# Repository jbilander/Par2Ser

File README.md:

# Amiga Par2Ser device

> 🚧 **Status: Proof of concept — working, not yet fast.** The link is
> verified end-to-end on real Rev 2A hardware in both directions: interactive
> terminal traffic and **kermit file transfers** both work (a 512 KB ROM image
> and a 906 KB binary have been transferred with essentially zero packet
> errors). Current throughput is roughly **3400 CPS transmit / 1400 CPS
> receive** (release build). That is not yet a win over the built-in serial
> port — a stock A500 runs kermit at 38400 baud (~3800 CPS) via `8n1.device` —
> so **throughput optimization is the active work**; the whole point of going
> through the parallel port is to beat that comfortably. There are no tagged
> releases until it does, so **build at your own risk** and expect the design
> to still change. PRs and issues welcome.

***
Rev. 2A <br />

***

A `serial.device`-compatible Amiga driver that bridges the parallel port to a
USB FIFO (FT240X) via Niklas Ekström's 2E parallel-adapter protocol, so unmodified
comms programs (c-kermit, NComm, …) can `set line par2ser.device`.

The hardware side is a small board built around a Lattice **LC4064V-75TN48C**
CPLD that speaks the 2E protocol to the Amiga and presents the bytes to an
**FT240X** USB FIFO. The PC sees a standard USB serial port (VCP).

## Repository layout

- **`amiga/`** — `par2ser.device` driver source (m68k, Bartman gcc).
- **`cpld/`** — Verilog firmware for the Lattice LC4064V CPLD.
  - `rtl/` — design sources (`par2ser_top.v`, `par2ser_fsm.v`).
  - `sim/` — Icarus Verilog smoke testbench.
  - `isplever/` — Lattice ispLEVER Classic 2.1 project files and pin
    constraints (`Par2Ser.lci`).
- **`KiCad/`** — KiCad 5.1 schematic and PCB sources (Rev 2A).
- **`FT_PROG/`** — FT_PROG template (`Par2Ser.xml`) capturing the
  FT240X MTP settings the bridge needs (VCP enabled, CBUS5 → CLK12MHz,
  product description). Open it in FT_PROG and apply to a fresh
  board to skip the manual click-through.
- **`images/`** — board photos and screenshots used in this README.
- **`Par2Ser_rev2a_schematic.pdf`** — exported schematic for quick
  reference without opening KiCad.

## Hardware overview (Rev 2A)

- **Lattice LC4064V-75TN48C** CPLD (48-pin TQFP, 64 macrocells, -75 speed)
- **FTDI FT240X** USB-to-parallel-FIFO (SSOP-24), USB-C connector
- **8-bit bidirectional buffer** between the Amiga DB-25 and the CPLD
- **JTAG header** for programming the CPLD via ispVM System with a
  cheap FT4232H-mini-module-based cable

The driver is built in the style of [SimpleDevice](https://github.com/jbilander/SimpleDevice)
for the Bartman `m68k-amiga-elf` (gcc 15.1) toolchain. The serial machinery
(receive ring buffer, `CMD_READ` satisfied from buffer, `SDCMD_QUERY` count
from a software counter) is ported from Iain Barclay's `8n1.device` 43.5.

It targets **Kickstart 1.3** (and up): the sources include `<ks13_compat.h>`,
which uses `#pragma GCC poison` to turn any accidental call to a KS 2.0+
library function into a compile error, so the driver stays loadable on an
unexpanded A500/A2000.

## Bill of Materials (Rev 2A)

Sourcing notes: most actives and precision passives are from
[Mouser](https://www.mouser.com/), the connectors and decorative
LEDs are inexpensive enough to come from AliExpress sellers (linked
examples below — any equivalent footprint works). Generic 0805/0603
passives can be substituted with any reputable manufacturer's part
matching the value, package, and dielectric/tolerance noted.

| Ref               | Qty | Value / Part         | Description                                    | Package        | Source                                                                                          | Notes                                                       |
|-------------------|-----|----------------------|------------------------------------------------|----------------|-------------------------------------------------------------------------------------------------|-------------------------------------------------------------|
| **U1**            | 1   | LC4064V-75TN48C      | Lattice ispMACH 4000V CPLD                     | 48-TQFP        | [Mouser 842-LC4064V75TN48C](https://www.mouser.com/ProductDetail/842-LC4064V75TN48C)             | 64 macrocells, -75 speed grade                              |
| **U2**            | 1   | FT240XS-R            | FTDI USB-to-parallel FIFO                      | SSOP-24        | [Mouser 895-FT240XS-R](https://www.mouser.com/ProductDetail/895-FT240XS-R)                       | USB 2.0 Full Speed; VCP driver                              |
| **U3**            | 1   | TLV75533PDBVR        | TI 3.3 V LDO regulator, 500 mA                 | SOT-23-5       | [Mouser 595-TLV75533PDBVR](https://www.mouser.com/ProductDetail/595-TLV75533PDBVR)               | Fixed 3.3 V output                                          |
| **J1**            | 1   | DB25 Male            | Right-angle PCB DB-25 (M)                      | Solder cups   | [AliExpress example](https://www.aliexpress.com/item/1005006354086316.html)                      | Amiga parallel port                                         |
| **J2**            | 1   | USB-C 2.0 (TYPE-C-02) | 16-pin USB-C, USB 2.0 only (no SuperSpeed)    | SMD + THM tabs | [AliExpress example](https://www.aliexpress.com/item/1005005371954812.html)                      | Common "TYPE-C-02" footprint                                |
| **J3**            | 1   | 2×5 pin header       | 2.54 mm pitch, 10-pin (2×5)                    | Through-hole   | [AliExpress example](https://www.aliexpress.com/item/1005001493183557.html)                      | Optional — can press-fit ribbon during programming          |
| **FB1**           | 1   | 600 Ω @ 100 MHz       | Ferrite bead                                   | 0805           | [Mouser 875-HZ0805E601R-10](https://www.mouser.com/ProductDetail/875-HZ0805E601R-10)              | USB VBUS filter                                             |
| **D1**            | 1   | Yellow LED           | Activity LED (optional)                        | 2×5×7 mm TH    | [AliExpress example](https://www.aliexpress.com/item/1005006220921860.html)                      | Lit when transaction in progress                            |
| **D2**            | 1   | Green LED            | Power LED (optional)                           | 2×5×7 mm TH    | [AliExpress example](https://www.aliexpress.com/item/1005006220921860.html)                      | 3.3 V rail indicator                                        |
| **D3**            | 1   | Red LED              | TX LED                                         | 0603 SMD       | [AliExpress example](https://www.aliexpress.com/item/1005005975741298.html)                      | Amiga → PC byte flow                                        |
| **D4**            | 1   | Red LED              | RX LED                                         | 0603 SMD       | [AliExpress example](https://www.aliexpress.com/item/1005005975741298.html)                      | PC → Amiga byte flow                                        |
| **RN1**           | 1   | 8×10 kΩ bussed (A09-103JP) | 9-pin SIP resistor network               | SIP-9          | [AliExpress example](https://www.aliexpress.com/item/1005006954621214.html)                      | Amiga D0..D7 pull-ups, one common                           |
| **RN2**           | 1   | 4×10 kΩ bussed (A05-103JP) | 5-pin SIP resistor network               | SIP-5          | [AliExpress example](https://www.aliexpress.com/item/1005006954621214.html)                      | Additional Amiga-side pull-ups                              |
| **RN3, RN4, RN5** | 3   | 4×330 Ω isolated     | 8-pin SMD isolated resistor array              | 1206-8         | [Mouser 652-CAY16-3300F4LF](https://www.mouser.com/ProductDetail/652-CAY16-3300F4LF)              | Series limiters on signal lines                             |
| **R1, R3, R4**    | 3   | 1 kΩ                 | LED current limiter / signal                   | 0805           | [Mouser 652-CR0805FX-1001ELF](https://www.mouser.com/ProductDetail/652-CR0805FX-1001ELF)          |                                                             |
| **R2**            | 1   | 10 kΩ                | Series for D2 power LED (high R = low brightness) | 0805        | [Mouser 652-CR0805FX-1002ELF](https://www.mouser.com/ProductDetail/652-CR0805FX-1002ELF)          | Matches green power-LED forward voltage                     |
| **R5**            | 1   | 33 Ω                 | CLKOUT line damping resistor                   | 0603           | [Mouser 652-CR0603FX-33R0ELF](https://www.mouser.com/ProductDetail/652-CR0603FX-33R0ELF)          | Common practice for clock lines, not per FT240X datasheet  |
| **R6**            | 0   | 330 Ω (**DNP**)      | Series on /STROBE — not populated              | 0805           | [Mouser 652-CR0805FX-3300ELF](https://www.mouser.com/ProductDetail/652-CR0805FX-3300ELF)          | **Do Not Place** — populate only if /STROBE used in fw      |
| **R7, R8**        | 2   | 5.1 kΩ               | USB-C CC1/CC2 pull-downs                       | 0805           | [Mouser 652-CR0805FX-5101ELF](https://www.mouser.com/ProductDetail/652-CR0805FX-5101ELF)          | Identifies device as USB 2.0 (sink)                         |
| **R9, R10**       | 2   | 27 Ω                 | USB D+/D− series                               | 0805           | [Mouser 652-CR0805FX-27R0ELF](https://www.mouser.com/ProductDetail/652-CR0805FX-27R0ELF)          | Per USB 2.0 Full Speed spec                                 |
| **R11**           | 1   | 4.7 kΩ               | Pull-down for TCK (JTAG)                       | 0805           | [Mouser 652-CR0805FX-4701ELF](https://www.mouser.com/ProductDetail/652-CR0805FX-4701ELF)          | Standard JTAG practice                                      |
| **R12**           | 1   | 10 kΩ                | Pull-up for SIWU#                              | 0603           | [Mouser 652-CR0603-JW-103ELF](https://www.mouser.com/ProductDetail/652-CR0603-JW-103ELF)          | Keeps SIWU# deasserted when CPLD pin 44 is high-Z           |
| **C1, C2**        | 2   | 4.7 µF, 10 V, X7R    | VBUS bulk / LDO input                          | 0805           | [Mouser 81-GRM21BR71A475KE1K](https://www.mouser.com/ProductDetail/81-GRM21BR71A475KE1K)          | Murata GRM21 X7R, 10 V                                      |
| **C3**            | 1   | 1 µF, X7R            | LDO output filter                              | 0805           |                                                                                                 | Per TLV75533 datasheet                                      |
| **C4, C5**        | 2   | 47 pF, C0G/NP0       | USB D+/D− noise filter                         | 0603           | [Mouser 791-0603N470G160CT](https://www.mouser.com/ProductDetail/791-0603N470G160CT)              | Tight tolerance important                                   |
| **C6, C7, C8**    | 3   | 0.1 µF, X7R          | Decoupling (0805 spots)                        | 0805           |                                                                                                 |                                                             |
| **C9 – C13**      | 5   | 0.1 µF, X7R          | Decoupling (0603 spots)                        | 0603           |                                                                                                 | One per VCC pin                                             |

**Distinct line items: 27** &nbsp;·&nbsp; **Components to populate: 37** (38 if /STROBE is wired up in a future firmware — see R6)

### Mounting and additional hardware

- The **LC4064V** is JTAG-programmable in-circuit — no socket needed.
- The **JTAG header (J3)** uses the standard Lattice 2×5 pinout —
  check `cpld/README.md` for the exact pinout and the recommended
  FT4232H-Mini-Module-based cable. The header doesn't have to be
  soldered down; you can press-and-hold the 2×5 ribbon cable
  against the pads during programming.

### 3D-printable case

A 3D-printable two-part case is provided in the `3D/` folder. It is
adapted from the former **SDBox-v2** case, slimmed down and made more
proportional — the Rev 2A design no longer has to house a bulky
Arduino Nano v3, so the enclosure is significantly thinner. The DB-25
exits one end and the USB-C port the other, and the top lid has two
holes for the panel LEDs: one for the **Power LED (green)** and one for
the **Activity LED (yellow)**.

| File | Description |
|------|-------------|
| `3D/Par2Ser.scdoc` | SpaceClaim source file for the case |
| `3D/Par2Ser.stp` | STEP export (top + bottom) for use in other CAD tools |
| `3D/Par2Ser_top.stl` | Top lid, ready to slice and print |
| `3D/Par2Ser_bottom.stl` | Bottom shell, ready to slice and print |
| `3D/Par2Ser_text.skp` | SketchUp source for the embossed "Par2Ser" lid text |

<table>
  <tr>
    <td align="center">
      <br />
      <sub>USB-C end, with the two LED holes in the top lid</sub>
    </td>
    <td align="center">
      <br />
      <sub>DB-25 end</sub>
    </td>
  </tr>
  <tr>
    <td align="center">
      <br />
      <sub>Side profile showing the slimmer enclosure</sub>
    </td>
    <td align="center">
      <br />
      <sub>PCB fitted into the bottom shell</sub>
    </td>
  </tr>
</table>

The renders above are from the CAD program. The case was printed on a
Creality Ender-3 Pro in white PLA. The build photos below show the
assembly steps and the finished unit fitted to an Amiga 500.

#### Fitting the panel LEDs

The two indicator LEDs are soldered last. Fit the **PWR (green, Power)**
and **ACT (yellow, Activity)** LEDs into their positions, then check
from the top that each one protrudes ever so slightly through its hole
in the case lid. Once the height looks right, tack down a single leg,
snip the leads flush, and only then solder both joints properly. Doing
it in that order keeps the LEDs sitting at the correct height instead of
being pushed in or standing too proud.

<table>
  <tr>
    <td align="center">
      <br />
      <sub>Test-fitting the green PWR and yellow ACT LEDs before tacking them down</sub>
    </td>
    <td align="center">
      <br />
      <sub>Underside of the finished board seated in the bottom shell</sub>
    </td>
  </tr>
</table>

#### Finished unit

<table>
  <tr>
    <td align="center">
      <br />
      <sub>Assembled case closed up, with the PWR/ACT LEDs visible through the lid</sub>
    </td>
    <td align="center">
      <br />
      <sub>Plugged into the A500 parallel port and connected to a PC over USB-C</sub>
    </td>
  </tr>
</table>

In the powered-on photo the green **PWR** LED is lit, and the red glow
bleeding through the lid is the FT240XS **RX/TX** LEDs shining through
the white PLA — here the blink firmware has the **TX** LED on. This is
something of a happy accident: if you don't want the glow, print the
case in black or another dark material, or simply leave the RX/TX LEDs
unpopulated.

> **Note:** The USB-C cut-out in the current print is slightly too wide.
> It's a cosmetic issue only — the port works fine — and will be tidied
> up shortly so the opening sits more symmetrically around the connector.

## Files (amiga/)

- `par2ser.c` — device skeleton + serial command set + receive ring buffer
- `transport.h` / `transport.c` — byte-pipe to the adapter (**stubbed** for now)
- `debug.c` — `KPrintF` over `RawDoFmt`/`RawPutChar` (verbatim from SimpleDevice)
- `Makefile`

## Build (amiga/)

```sh
cd amiga
make debug      # build-debug/par2ser.device, with KPrintF tracing
make release    # build-release/par2ser.device, stripped
```

Adjust `INCDIRS` for your NDK path as in SimpleDevice.

## Programming the FT240X (one-time, before first use)

The CPLD needs a 12 MHz clock from the FT240X to operate. By default
the FT240X's CBUS5 pin is **not** configured as a clock output — you
have to set its function in the chip's internal MTP (one-time-programmable)
memory using FTDI's **FT_PROG** utility. While you're at it, you should
also tell the chip to advertise itself as a Virtual COM Port (VCP) so
that comms software on the host can open it as a regular serial port,
and you can optionally set a friendly USB product-description string.

These settings are all stored on the FT240X chip itself — they
persist across power cycles and across host machines.

### What you'll need

- FTDI **FT_PROG** (free download from <https://ftdichip.com/utilities/>;
  requires .NET Framework 4.0 or newer, which is included with
  Windows 8.1 and above)
- The Rev 2A board, powered via USB, on a Windows machine (FT_PROG
  is Windows-only; users on Linux/macOS can use a Windows VM, or
  the open-source `ftdi_eeprom` from libftdi as an alternative —
  see note at the end of this section)

### Install FT_PROG

Download FT_PROG from <https://ftdichip.com/utilities/> (current version
at time of writing: 3.12.75.692). Extract the ZIP, run the installer,
click through to **Finish**:

### Fast path: apply the supplied template

The `FT_PROG/Par2Ser.xml` file in this repo is a saved FT_PROG template
with all the settings the Par2Ser bridge needs (VCP enabled, CBUS5 →
CLK12MHz, CBUS6 → Keep_Awake#, Product Description → `Par2Ser USB Serial`).
The fast path is:

1. Plug the Rev 2A board into a Windows PC via USB-C. Windows will
   detect the FT240X and bind FTDI's bus-level driver, presenting
   the device as **"USB Serial Converter"** under
   *Universal Serial Bus controllers* in Device Manager.
2. Launch FT_PROG and **FILE → Open** the `FT_PROG/Par2Ser.xml`
   template — this loads the desired settings into FT_PROG's editor.
3. **DEVICES → Scan and Parse** (<kbd>Ctrl+P</kbd>) to bring the
   live chip's current settings under the same editor.
4. **DEVICES → Program** to apply the template values to the chip
   — confirm the success dialog appears.
5. Unplug and replug the board.

If you'd rather understand or customize each setting, walk through
the manual steps below instead.

### Manual walkthrough (step-by-step)

1. Plug the Rev 2A board into a Windows PC via USB-C. Windows will
   detect the FT240X and bind FTDI's bus-level driver, presenting
   the device as **"USB Serial Converter"** under
   *Universal Serial Bus controllers* in Device Manager. (Whether
   a COM port appears at this stage depends on the host's driver
   state — see "Driver behavior across operating systems" below.)

2. Launch FT_PROG. Click **DEVICES → Scan and Parse** (or
   <kbd>Ctrl+P</kbd>). The device tree on the left should populate
   with the FT240X, and the lower pane shows the EEPROM contents
   dump:

3. Enable the **VCP driver mode**: in the device tree, expand
   **Hardware Specific → Port A → Driver** and select the
   **Virtual COM Port** radio button (it may be on "D2XX Direct"
   by default):

4. Configure the **CBUS5 clock output**: navigate to
   **Hardware Specific → CBUS Signals** and set the **C5** drop-down
   to **`CLK12MHz`**. The C6 drop-down can be left at its default
   (`Keep_Awake#`) — CBUS6 is wired to the CPLD but not used by the
   current firmware:

5. (Optional) Update the **USB String Descriptors** to identify the
   device as a Par2Ser. Setting the *Product Description* to
   `Par2Ser USB Serial` makes it easier to find when several FTDI
   devices are plugged into the same host. The factory-assigned
   *Serial Number* is unique per chip and stable — useful when
   binding driver settings or `udev` rules per device:

6. Click **DEVICES → Program** (the lightning-bolt icon). The
   *Program Devices* dialog shows the chip type, VID/PID, and the
   strings about to be written to MTP. Confirm the values look right
   and click **Program**:

   You should see **"Programming Successful"** at the bottom of the
   dialog when the write completes:

7. Unplug and replug the board. Windows will re-enumerate the device.

### Verifying the configuration

After the FT_PROG round-trip, you can confirm the chip is configured
correctly with one or both of:

**A. Oscilloscope check of the 12 MHz clock.** With the board powered
via USB, probe the trace at R5 (the damping resistor on the CPLD's
clock input). You should see a clean ~12 MHz square wave near rail-to-rail
on a 3.3 V LVTTL swing:

The small overshoot/ringing on the edges is the scope probe's ground-lead
inductance, not a problem with the signal — using a probe ground spring
close to the test point cleans it up. The signal is well within LVTTL
input tolerances at the CPLD's pin 43.

**B. COM-port enumeration check on the host.** The board should appear
as a serial port. The device name varies by OS — see below.

### Driver behavior across operating systems

The FT_PROG settings live on the chip; *whether* a given host then
makes them visible as a normal COM/tty port depends on what FTDI driver
support that host has. Tested behavior so far:

| Host                    | Result                                  | Driver intervention needed |
|-------------------------|-----------------------------------------|----------------------------|
| **macOS 10.15 Catalina** | `/dev/cu.usbserial-XXXXXXXX` on plug-in | None — Apple's built-in `AppleUSBFTDI` driver handles it |
| **Linux** (Pop!\_OS, Ubuntu, similar) | `/dev/ttyUSB0` on plug-in     | None — the in-kernel `ftdi_sio` module binds automatically |
| **Windows 10/11**       | `USB Serial Port (COMn)` under *Ports (COM & LPT)* | Typically none — Windows Update pushes the FTDI CDM (Combined Driver Model) package automatically |
| **Windows 8.1**         | Depends on the machine's history (see below) | One-time CDM install on a fresh host |

The Windows 8.1 case is the only one with a footgun, and it's
machine-specific rather than OS-specific. On Windows 8.1, the **CDM
(Combined Driver Model)** package — which contains both the bus-level
driver (`USB Serial Converter`) *and* the VCP layer that creates the
COM port — is not bundled with the OS. It can be installed via
Windows Update, but isn't always pushed automatically.

In our testing on two Windows 8.1 SP2 machines:

- **Machine A**: had previously hosted other FTDI devices. When the
  Par2Ser board was first plugged in, Windows auto-installed both
  the USB Serial Converter and the VCP layer, and a COM port
  (`COM4`) appeared under *Ports (COM & LPT)* immediately. The
  "Installing Par2Ser USB Serial" progress dialog appeared
  automatically:

  After the install, Device Manager's Events tab on the resulting
  `USB Serial Port (COMn)` entry shows the FTDI VCP driver service
  `FTSER2K` being registered and `ftdiport.inf` driving the COM-port
  instance — the proof that the VCP layer attached on top of the
  bus-level driver:

- **Machine B**: had not previously had an FTDI device on it.
  Plugging in the Par2Ser board only created the *USB Serial
  Converter* entry under *Universal Serial Bus controllers*; no COM
  port appeared. **The fix on this machine turned out to be very
  simple**: right-click *USB Serial Converter* in Device Manager,
  choose **Uninstall**, in the dialog that appears **leave the
  "Delete the driver software for this device" checkbox unchecked**,
  click OK, then unplug and replug the board. Windows re-enumerated
  the device, picked up the VCP driver this time, and `COM10`
  appeared under *Ports (COM & LPT)*. Total time: about 30 seconds.

  This "uninstall (keep files) then replug" trick works on a Win8.1
  machine that has the FTDI VCP driver files present on disk but
  somehow bound only the bus-level driver on the first plug-in.
  The driver files are kept; only the device-to-driver binding is
  cleared, so the next enumeration can re-pick the correct (full)
  driver stack.

**If you're on Windows 8.1 (or earlier) and no COM port appears**,
try the uninstall-without-deleting-files trick first — it's quick
and reversible. If that doesn't work (the VCP driver files truly
aren't present on the machine), install FTDI's CDM driver package
from <https://ftdichip.com/drivers/vcp-drivers/> — download the
*setup executable*, unplug the board, run the installer, replug.
After that the COM port will appear on every subsequent plug-in.
The MTP setting in the chip stays correct throughout; only the
host needs the right driver layer bound.

On Linux and macOS, no equivalent step is needed — the driver shipped
with the OS supports the FT240X out of the box.

### Linux/macOS alternative for the MTP programming (libftdi)

On non-Windows systems, the MTP programming (CBUS5 → CLK12MHz, VCP
enable, etc.) can be done with `ftdi_eeprom` from the `libftdi`
package — but it has not been tested by the author of this repo.
You'd need a small config file pointing at the FT240X (matched by
VID/PID `0403:6015`) and setting `cbus5=CLK12`. See the libftdi
documentation for the exact syntax.

The simplest path for now is to do the one-time FT_PROG step on any
available Windows machine. Once the FT240X's MTP is programmed, the
chip behaves identically on any host.

## Programming the CPLD via JTAG

The LC4064V is programmed in-circuit via the 2x5 JTAG header (J3)
using **ispVM System** (the legacy Lattice programming tool, bundled
with the free ispLEVER Classic install). For the JTAG cable, an
inexpensive **FT4232H Mini Module** works well as a generic FTDI
cable that ispVM recognizes as `USB2 / FTUSB-0` without needing any
EEPROM modification.

### Wiring (FT4232H Mini Module ↔ Par2Ser J3)

The FT4232H's channel A MPSSE pins map to JTAG signals as follows:

| FT4232H Mini Module | JTAG signal | Par2Ser J3 pin |
|---------------------|-------------|----------------|
| **AD0** (ADBUS0)    | TCK         | pin 1 (TCK)    |
| **AD1** (ADBUS1)    | TDI         | pin 5 (TDI)    |
| **AD2** (ADBUS2)    | TDO         | pin 7 (TDO)    |
| **AD3** (ADBUS3)    | TMS         | pin 3 (TMS)    |
| any GND on module   | GND         | pin 2 or 4     |

Do NOT connect the FT4232H's 3.3 V or 5 V output to J3 — the
Par2Ser self-powers from USB-C and J3 pin 6 (3V3) is an output
from the board, not a power input.

The J3 header doesn't have to be soldered down — you can press
the 2x5 ribbon connector (or individual jumper wires) against the
through-hole pads with gentle hand-held force during programming.

*Note: RN2, the 10 kΩ pull-up network for TMS, can be left
unpopulated and JTAG will still work. The FT4232H actively drives
TMS during programming, and the LC4064V has a weak internal
pull-up on TMS per IEEE 1149.1. RN2 should still be populated
before final use for noise immunity when the JTAG cable is
disconnected.*

### Driver setup (Windows)

For ispVM to talk to the JTAG cable, **channel A (Interface 0) of
the FT4232H must be bound to FTDI's D2XX driver** (not
libusb-win32, WinUSB, or libusbK). The other three interfaces
(B/C/D) are not used by ispVM and can stay bound to whatever
driver they had previously.

After plugging in the Mini Module, open Device Manager and locate
the four "Quad RS232-HS" entries (Interface 0/1/2/3). If
Interface 0 is bound to the wrong driver — for example, listed
under *libusb-win32 device* (a typical leftover from a previous
OpenOCD session) rather than under *Universal Serial Bus
controllers* — rebind it:

1. Right-click **Quad RS232-HS (Interface 0)** → **Update Driver
   Software** → **Browse my computer for driver software** →
   **Let me pick from a list of devices on my computer**.
2. Select **USB Serial Converter A** (FTDI's D2XX driver, version
   2.12.36.4 or newer).
3. Click Next. Windows will rebind Interface 0 to the D2XX driver
   without affecting Interfaces 1–3.
4. **Restart ispLEVER/ispVM** — without this, the running ispVM
   process still has the old driver state cached and will not see
   the cable.

After the rebind, Device Manager should show one entry as
`USB Serial Converter A` under *Universal Serial Bus controllers*
(Interface 0, the one ispVM will use), and the other three
interfaces (1/2/3) wherever they were before — that's fine, they're
not used for JTAG.

### Programming procedure

1. **Power the Par2Ser from a USB charger**, not from the same PC
   running ispVM. This is important: if the Par2Ser is plugged into
   the same Windows host that is running ispVM, both FTDI devices
   (the Par2Ser's FT240X and the FT4232H Mini Module) appear as
   "USB Serial Converter" entries, and ispVM can grab the wrong one.
   Powering Par2Ser from a separate USB charger keeps it powered
   while leaving only the FT4232H Mini Module visible to ispVM.

2. **Connect the JTAG cable** per the wiring table above, with the
   FT4232H Mini Module plugged into the Windows PC.

3. **Launch ispVM System** (Start Menu → Lattice Semiconductor →
   ispVM System).

4. **Scan Board** (toolbar button) — should detect the LC4064V and
   show it as `LC4064V(B)-32IO` in the chain. (The `(B)-32IO` is
   ispVM's internal name for the 64-macrocell, 32-IO variant — your
   physical chip is the TQFP48 package of that die.)

5. **Double-click the device row** in the chain → set **Data File**
   to the `.jed` file generated by the ispLEVER fitter → set
   **Operation** to *Erase, Program, Verify*.

6. **(Important) Slow down TCK for flywire JTAG.** Open
   **Project → Project Settings → Advanced** and set
   **TCK Low Pulse Width Delay** to **3** or higher. The default
   15 MHz TCK is too fast for the typical flywire connection from
   the FT4232H to J3 — the verify step will fail with all-zeros
   readback on TDO. Stretching the TCK low-pulse by 3× makes
   programming reliable. Note that this setting is **per-project
   in ispVM**, so it has to be set again when switching projects.

7. **Click GO** (green arrow). Programming should complete in 3–10
   seconds with "Operation: Successful" and a green PASS in the
   Status column.

If the TCK Low Pulse Width Delay setting is left at the default
(1) and Debug mode is off, you'll see a `Failed in Function
VERIFY_USERCODE` error in the log, with received TDO reading all
zeros where the expected pattern was the programmed bitstream.
That's the signature of marginal TCK timing on flywire JTAG;
increasing the TCK Low Pulse Width Delay is the fix. (Enabling
Debug mode also happens to make programming work — the per-
transaction logging on the PC side adds enough pacing between
JTAG operations to mask the signal-integrity issue — but that's
an incidental workaround. The proper fix is the TCK delay
setting.)

## Milestone 1 — does kermit accept it? (no hardware needed) ✅

This milestone is **done**. It validates the driver in WinUAE without
any hardware:

1. `make debug` in `amiga/`, copy `build-debug/par2ser.device` to `DEVS:`
   in WinUAE.
2. Open a serial debug console (the same `RawPutChar` path SimpleDevice
   uses).
3. In kermit: `set line par2ser.device`. The trace shows `do_open()`,
   then the commands kermit issues (`SDCMD_SETPARAMS`, `SDCMD_QUERY`, …)
   with their parameters and the status word we return.

In this milestone `transport_write()` discards bytes (reports them sent)
and no RX data ever arrives, so a `CMD_READ` will stay pending — expected
with no hardware. The goal is purely to confirm acceptance and observe
the negotiation, especially the carrier check.

## Carrier / `/CD` handling

kermit checks carrier-detect before it will use the line. We have no real
CIA serial lines on the parallel port, so `SDCMD_QUERY` **synthesizes**
the status word. `serial.device` returns the raw (active-low) CIA-B
control lines, i.e. `0` = signal asserted, so the default
`ST_CARRIER_PRESENT = 0` reports CD/CTS/DSR all asserted.

The full word is `KPrintF`'d in `sdcmd_Query`, so if kermit reports
**NO CARRIER**, flip the polarity in `par2ser.c`:
```c
#define ST_CARRIER_PRESENT  ST_CD   /* try this if 0 doesn't satisfy kermit */
```
and compare the logged status against what kermit expects.

## Milestone 2 — real adapter ✅ (bidirectional, file transfers working)

### Transmit — working on hardware ✅

The Amiga → PC direction is verified on a real Rev 2A board: typing in
c-kermit (`cki196`) after `set line par2ser.device` / `connect` produces the
characters in a PC terminal on the FT240X's USB serial port, with the driver's
`KPrintF` trace confirming each `CMD_WRITE`.

Bring-up steps:

1. Build the CPLD firmware in ispLEVER Classic 2.1 — see `cpld/README.md`
   for details. The result is a `par2ser.jed` file.
2. Program the FT240X's CBUS5 to CLK12MHz output (see above).
3. Program the CPLD via ispVM System using a JTAG cable.
4. Build the driver with `make debug` in `amiga/` (the `Makefile` has
   `-DPAR2SER_HW` and the adapter objects enabled), copy
   `build-debug/par2ser.device` to `DEVS:`.

The low-level transport lives in `amiga/low-lib/` (`adapter.c`, `adapter.h`,
`adapter_low.s`). It is derived from Niklas Ekström's parallel-adapter
transport but renamed and reworked for Par2Ser: it is a byte-pipe, not SPI,
so the chip-select / card-present / speed-switch machinery was removed, the
fast-path assembly was ported from vasm to GNU-as syntax for the
`m68k-amiga-elf` toolchain, and the SD-card init was replaced with a plain
parallel-port grab. The WRITE1/READ1 command encoding and the SELECT/POUT/BUSY
handshake are unchanged and are decoded bit-for-bit by the CPLD FSM.

One hardware bug surfaced during TX bring-up and is fixed in the current RTL:
the FT240X write strobe was firing one clock before the CPLD drove the data
bus, so the chip latched a floating bus and bytes arrived as garbage. Driving
the data across the WR pulse (setup + hold around the falling edge) fixed it;
see `cpld/rtl/par2ser_fsm.v`.

### Receive — working on hardware ✅

The PC → Amiga direction also works: characters typed in a PC terminal appear
in c-kermit on the Amiga, and kermit file transfers complete in both
directions (`PAR2SER_RX_ENABLED` is 1 in `transport.h`).

One further bug had to be fixed before file transfers would run, and it was
pure protocol logic rather than hardware: `read_copy()` completed a `CMD_READ`
only once `io_Actual >= io_Length`, but kermit posts reads with a large buffer
(e.g. 9064 bytes) as a *maximum*, expecting back whatever has arrived. Every
packet's bytes landed in the ring correctly — zero overruns, exact counts —
and then the read sat pending forever waiting to fill the buffer, so kermit
timed out and retried every packet ("?Too many retries"). The Amiga
byte-stream convention is the opposite (console.device: *"if there is some
input, but not as much as can fill io_Length, the request will be satisfied
with the input currently available"*); completing the read as soon as any byte
has been delivered made transfers work immediately.

RX design: the adapter's ACK line (open-drain, DB25 pin 10) connects only to
**CIA-A /FLAG**, an interrupt-only CIA input — confirmed against the KiCad
netlist — so there is no readable doorbell level; the FLAG interrupt itself is
the data-available signal. The driver registers on the FLAG ICR bit via
**cia.resource** (`AddICRVector`, see `amiga/low-lib/cia_protos.h`) rather
than an `INTB_PORTS` server, so only genuine FLAG events are dispatched and
the shared ICR is owned correctly. The handler reads exactly **one byte per
FLAG**: the CPLD's IDLE-gated ACK re-asserts after each READ1 completes if
the FIFO still holds data, producing a fresh /FLAG edge per remaining byte —
the drain is hardware-self-clocking, no loop in the interrupt. A one-shot
`transport_rx_prime()` at device-open regenerates the doorbell edge for any
data that arrived before the interrupt was enabled (the CIA latches edges,
not levels).

Getting RX to work surfaced and fixed several deep bugs, documented in the
commit history — most notably a **gcc calling-convention trap**: `asm("reg")`
parameter annotations are honored on function *definitions* but silently
ignored on *prototypes*, so cross-file calls into the adapter transfer
functions passed garbage in a0/d0 (every READ1 scribbled memory through a
junk pointer; TX had only appeared correct by register coincidence). The
adapter API now uses the plain C convention, with explicit register variables
+ inline `jsr` shims only at the true `adapter_low.s` asm boundary. On the
CPLD side, the READ handshake was reworked: never drive the Amiga bus before
its first POUT edge (eliminating microseconds of bus contention against the
CIA on every read), present one byte per edge and hold it across the CIA's
~1.4 µs read, and capture FT240X data while RD# is still low. 58/64
macrocells, timing met with 72 ns slack.

### Throughput — the active work 🚧

File transfers work; making them *fast* is what remains. Measured with
kermit on a real Rev 2A board, release builds:

| direction | CPS | notes |
| --------- | --- | ----- |
| TX (Amiga `send`) | ~3400 | after cutting the per-byte delay |
| RX (Amiga `get`)  | ~1400 | one FLAG interrupt per byte |

Target: comfortably past 38400 baud equivalent (~3800 CPS), since that is what
`8n1.device` already achieves on the built-in serial port.

What has been done and what is left:

- **Never benchmark a DEBUG build.** `KPrintF` goes out the real serial port
  at 9600 baud *synchronously*, ~1 ms per character, from inside the driver
  (and the receive ISR). A debug build measured ~570 CPS **with thousands of
  kermit retransmissions** — the debug spew was slow enough to time kermit out
  mid-packet. The same code in a release build ran ~3× faster with zero
  errors. Always `make release` for anything timing-related.
- **Per-byte TX delay (done).** `adapter_write_slow()` inherited a ~45 µs
  busy-wait per byte from Niklas's SD-card timing (~32 µs/byte at 250 kHz
  SPI) — irrelevant to this hardware. Cutting it to ~5.6 µs
  (`TX_BYTE_DELAY`, a tunable in `low-lib/adapter.c`) took TX from ~1900 to
  ~3400 CPS with no increase in errors. The floor has not been found yet;
  the knob can still be swept toward zero.
- **RX per-byte interrupt overhead (next, and the bigger prize).** Receive
  takes a full CIA-A FLAG interrupt per byte: dispatch, handler, one READ1
  transaction, `service_reads`, `ReplyMsg` — all for one byte. That overhead,
  not the inter-byte delay, is the RX ceiling. The fix is burst-draining
  several bytes per interrupt, which needs a way to know when to stop — i.e.
  a CPLD status command exposing "FIFO not empty" (there is macrocell
  headroom now: 58/64).
- **Fast-path assembly (unused).** `adapter_low.s` is built and linked but
  never called — `current_speed` stays SLOW, so the C bit-bang path runs.
  The asm clocks bytes with no inter-byte delay at all. Note it masks
  interrupts internally, so it is task-context only as written and would need
  rework before the receive ISR could use it.
- **Block streaming (later).** The >64-byte WRITE2/READ2 commands are not
  implemented in the current LC4064V FSM (D7=1 routes to `S_DRAIN`), so every
  transfer is chunked at 64 bytes. A whole kermit packet as one framed block
  would cut per-transaction overhead considerably — this is where a larger
  CPLD or a bespoke, parallel-tailored protocol would earn its keep.

### Other known issues

- **TX LED never visibly lights**: `led_tx` follows `drive_ft_d`, which is
  high ~166 ns per byte — too short to see. The RX and activity LEDs blink
  only briefly for the same reason. A pulse-stretcher counter in the CPLD
  (~50 ms per event) would fix all three; there is macrocell headroom now.
- Non-ASCII characters (å/ä/ö) may display wrong on the PC — check the
  Windows console codepage (the link itself is 8-bit clean).

## Credits

- **Niklas Ekström** — the 2E par-to-spi protocol and the SDBox
  adapter that this project is derived from. See his
  [amiga-par-to-spi-adapter](https://github.com/niklasekstrom/amiga-par-to-spi-adapter).
- **Iain Barclay** — `8n1.device` 43.5, the serial machinery template.
- **Bartman** — the `m68k-amiga-elf` toolchain.

## License

Licensed under [Creative Commons Attribution-ShareAlike 4.0 International](https://creativecommons.org/licenses/by-sa/4.0/)
(CC-BY-SA 4.0). You're free to use, modify, and redistribute this work
(including commercially), provided you give appropriate credit and
distribute derivative works under the same license.

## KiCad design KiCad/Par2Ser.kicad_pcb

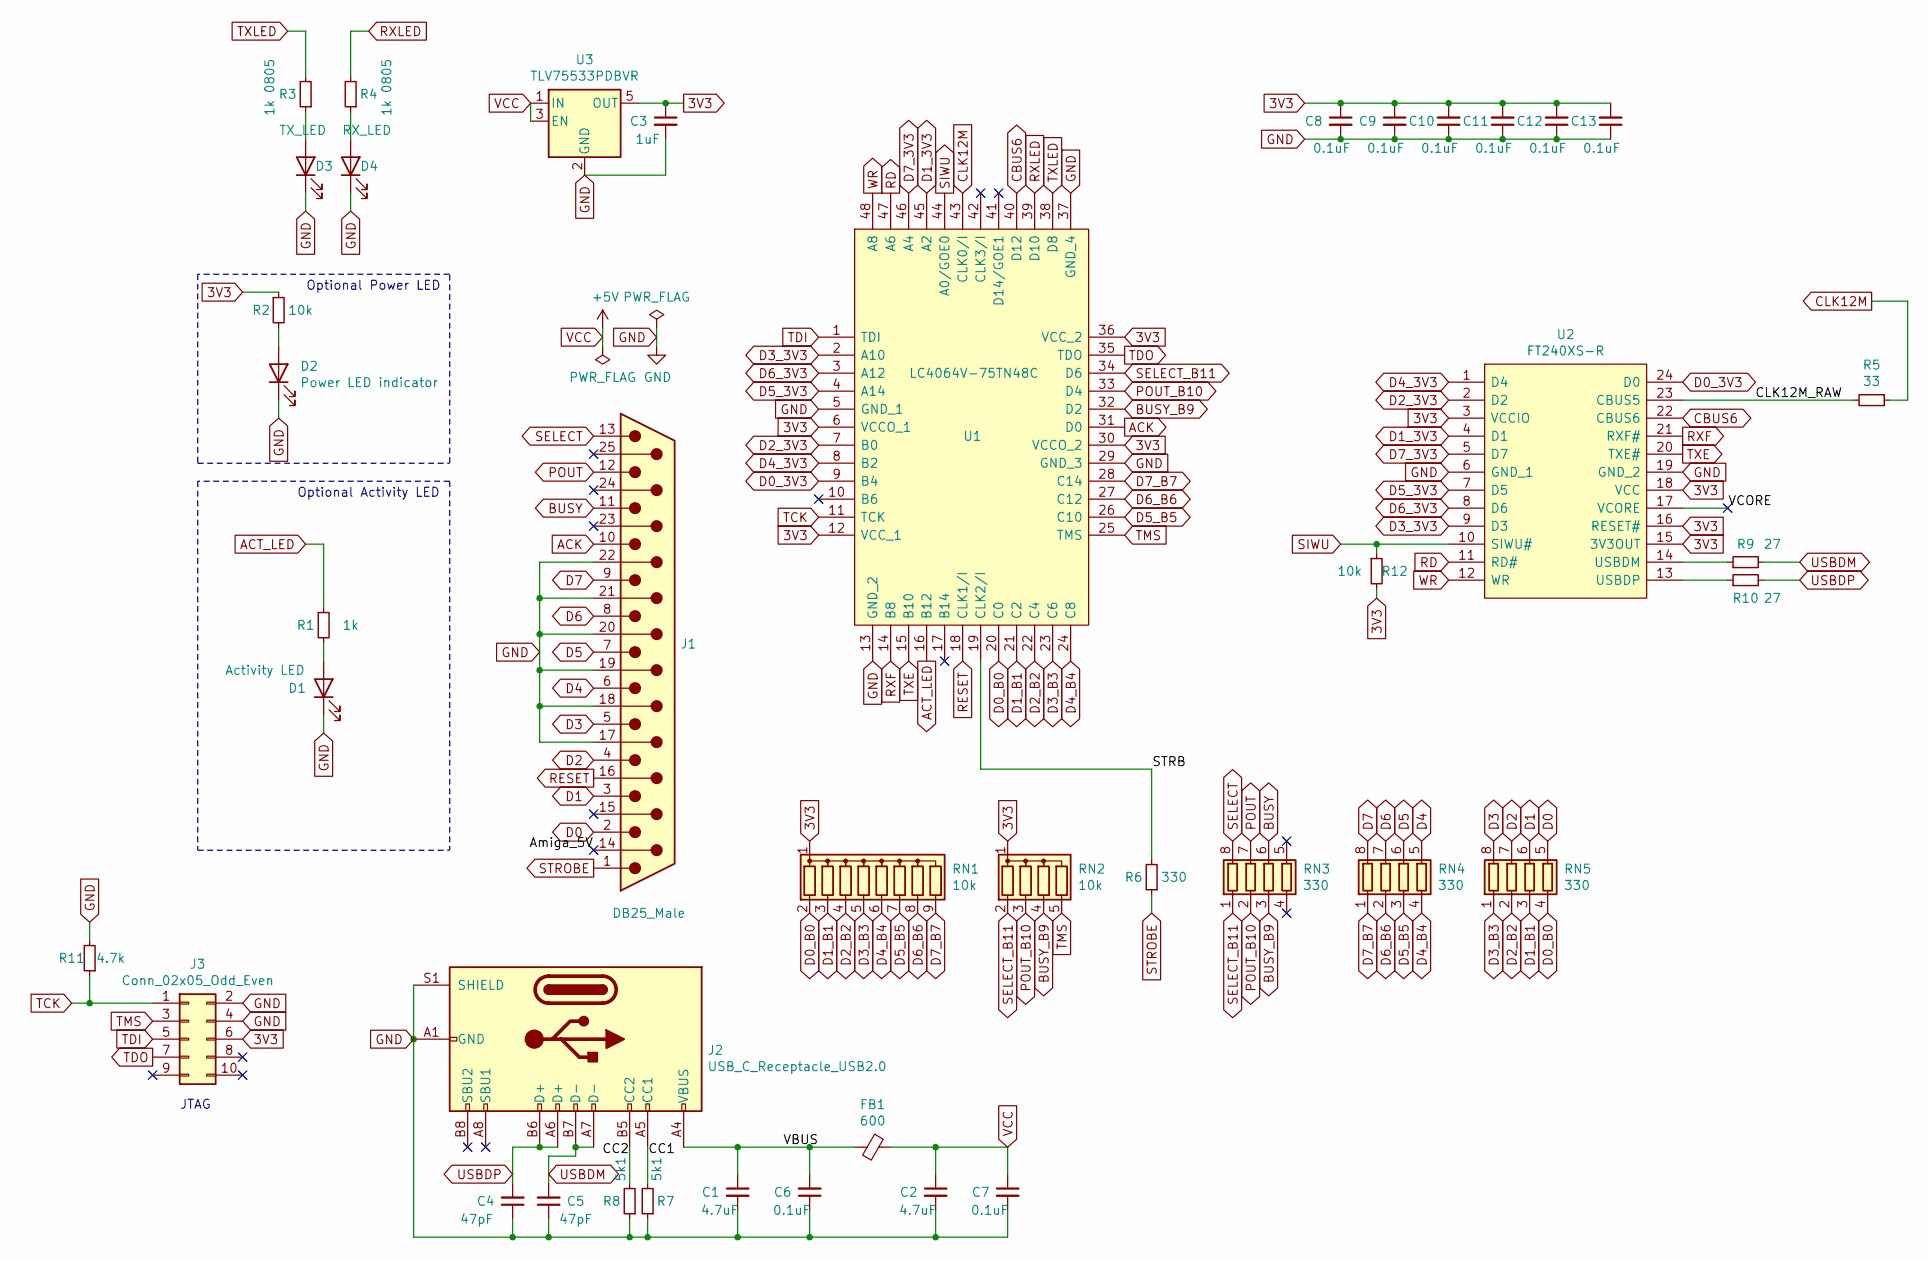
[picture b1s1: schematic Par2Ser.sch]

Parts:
C1, C2: 4.7uF; C_0805_2012Metric_Pad1.18x1.45mm_HandSolder
C3: 1uF; C_0805_2012Metric_Pad1.18x1.45mm_HandSolder
C4, C5: 47pF; C_0603_1608Metric_Pad1.08x0.95mm_HandSolder
C6, C7, C8: 0.1uF; C_0805_2012Metric_Pad1.18x1.45mm_HandSolder
C9, C10, C11, C12, C13: 0.1uF; C_0603_1608Metric_Pad1.08x0.95mm_HandSolder
D1: Activity LED; LED_Rectangular_W5.0mm_H2.0mm
D2: Power LED indicator; LED_Rectangular_W5.0mm_H2.0mm
D3: TX_LED; D_0603_1608Metric_Pad1.05x0.95mm_HandSolder
D4: RX_LED; D_0603_1608Metric_Pad1.05x0.95mm_HandSolder
FB1: 600; L_0805_2012Metric_Pad1.15x1.40mm_HandSolder
J1: DB25_Male; DSUB-25_Male_EdgeMount_P2.77mm
J2: USB_C_Receptacle_USB2.0; USB_C_Receptacle_HRO_TYPE-C-31-M-12
J3: Conn_02x05_Odd_Even; PinHeader_2x05_P2.54mm_Vertical
R1: 1k; R_0805_2012Metric_Pad1.20x1.40mm_HandSolder
R2: 10k; R_0805_2012Metric_Pad1.20x1.40mm_HandSolder
R3, R4: 1k 0805; R_0805_2012Metric_Pad1.20x1.40mm_HandSolder
R5: 33; R_0603_1608Metric_Pad0.98x0.95mm_HandSolder
R6: 330; R_0805_2012Metric_Pad1.20x1.40mm_HandSolder
R7, R8: 5k1; R_0805_2012Metric_Pad1.20x1.40mm_HandSolder
R9, R10: 27; R_0805_2012Metric_Pad1.20x1.40mm_HandSolder
R11: 4.7k; R_0805_2012Metric_Pad1.20x1.40mm_HandSolder
R12: 10k; R_0603_1608Metric_Pad0.98x0.95mm_HandSolder
RN1: 10k; R_Array_SIP9
RN2: 10k; R_Array_SIP5
RN3, RN4, RN5: 330; R_Array_Convex_4x0603
U1: LC4064V-75TN48C; TQFP-48_7x7mm_P0.5mm
U2: FT240XS-R; SSOP-24_3.9x8.7mm_P0.635mm
U3: TLV75533PDBVR; SOT-23-5

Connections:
3V3: C3.1, C8.1, C9.1, C10.2, C11.2, C12.2, C13.2, J3.6, R2.1, R12.2, RN1.1 (common), RN2.1 (common), U1.6 (VCCO_1), U1.12 (VCC_1), U1.30 (VCCO_2), U1.36 (VCC_2), U2.3 (VCCIO), U2.15 (3V3OUT), U2.16 (RESET#), U2.18 (VCC), U3.5 (OUT)
/Amiga_5V: J1.14
/CC1: J2.A5 (CC1), R7.2
/CC2: J2.B5 (CC2), R8.2
/CLK12M_RAW: R5.2, U2.23 (CBUS5)
/STRB: R6.2, U1.19 (CLK2/I)
/VBUS: C1.1, C6.2, FB1.2, J2.A4 (VBUS), J2.A9 (VBUS), J2.B4 (VBUS), J2.B9 (VBUS)
/VCORE: U2.17 (VCORE)
ACK: J1.10, U1.31 (D0)
ACT_LED: R1.1, U1.16 (B12)
BUSY: J1.11, RN3.6 (R3.2)
BUSY_B9: RN2.4 (R3), RN3.3 (R3.1), U1.32 (D2)
CBUS6: U1.40 (D12), U2.22 (CBUS6)
CLK12M: R5.1, U1.43 (CLK0/I)
D0: J1.2, RN5.5 (R4.2)
D0_3V3: U1.9 (B4), U2.24 (D0)
D0_B0: RN1.2 (R1), RN5.4 (R4.1), U1.20 (C0)
D1: J1.3, RN5.6 (R3.2)
D1_3V3: U1.45 (A2), U2.4 (D1)
D1_B1: RN1.3 (R2), RN5.3 (R3.1), U1.21 (C2)
D2: J1.4, RN5.7 (R2.2)
D2_3V3: U1.7 (B0), U2.2 (D2)
D2_B2: RN1.4 (R3), RN5.2 (R2.1), U1.22 (C4)
D3: J1.5, RN5.8 (R1.2)
D3_3V3: U1.2 (A10), U2.9 (D3)
D3_B3: RN1.5 (R4), RN5.1 (R1.1), U1.23 (C6)
D4: J1.6, RN4.5 (R4.2)
D4_3V3: U1.8 (B2), U2.1 (D4)
D4_B4: RN1.6 (R5), RN4.4 (R4.1), U1.24 (C8)
D5: J1.7, RN4.6 (R3.2)
D5_3V3: U1.4 (A14), U2.7 (D5)
D5_B5: RN1.7 (R6), RN4.3 (R3.1), U1.26 (C10)
D6: J1.8, RN4.7 (R2.2)
D6_3V3: U1.3 (A12), U2.8 (D6)
D6_B6: RN1.8 (R7), RN4.2 (R2.1), U1.27 (C12)
D7: J1.9, RN4.8 (R1.2)
D7_3V3: U1.46 (A4), U2.5 (D7)
D7_B7: RN1.9 (R8), RN4.1 (R1.1), U1.28 (C14)
GND: C1.2, C2.2, C3.2, C4.1, C5.1, C6.1, C7.2, C8.2, C9.2, C10.1, C11.1, C12.1, C13.1, D1.1 (K), D2.1 (K), D3.1 (K), D4.1 (K), J1.17, J1.18, J1.19, J1.20, J1.21, J1.22, J2.A1 (GND), J2.A12 (GND), J2.B1 (GND), J2.B12 (GND), J2.S1 (SHIELD), J3.2, J3.4, R7.1, R8.1, R11.2, U1.5 (GND_1), U1.13 (GND_2), U1.29 (GND_3), U1.37 (GND_4), U2.6 (GND_1), U2.19 (GND_2), U3.2 (GND)
unnamed: D1.2 (A), R1.2
unnamed: D2.2 (A), R2.2
unnamed: D3.2 (A), R3.1
unnamed: D4.2 (A), R4.1
unnamed: R9.1, U2.14 (USBDM)
unnamed: R10.1, U2.13 (USBDP)
POUT: J1.12, RN3.7 (R2.2)
POUT_B10: RN2.3 (R2), RN3.2 (R2.1), U1.33 (D4)
RD: U1.47 (A6), U2.11 (RD#)
RESET: J1.16, U1.18 (CLK1/I)
RXF: U1.14 (B8), U2.21 (RXF#)
RXLED: R4.2, U1.39 (D10)
SELECT: J1.13, RN3.8 (R1.2)
SELECT_B11: RN2.2 (R1), RN3.1 (R1.1), U1.34 (D6)
SIWU: R12.1, U1.44 (A0/GOE0), U2.10 (SIWU#)
STROBE: J1.1, R6.1
TCK: J3.1, R11.1, U1.11 (TCK)
TDI: J3.5, U1.1 (TDI)
TDO: J3.7, U1.35 (TDO)
TMS: J3.3, RN2.5 (R4), U1.25 (TMS)
TXE: U1.15 (B10), U2.20 (TXE#)
TXLED: R3.2, U1.38 (D8)
USBDM: C5.2, J2.A7 (D-), J2.B7 (D-), R9.2
USBDP: C4.2, J2.A6 (D+), J2.B6 (D+), R10.2
VCC: C2.1, C7.1, FB1.1, U3.1 (IN), U3.3 (EN)
WR: U1.48 (A8), U2.12 (WR)

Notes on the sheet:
Optional Activity LED
Optional Power LED
JTAG

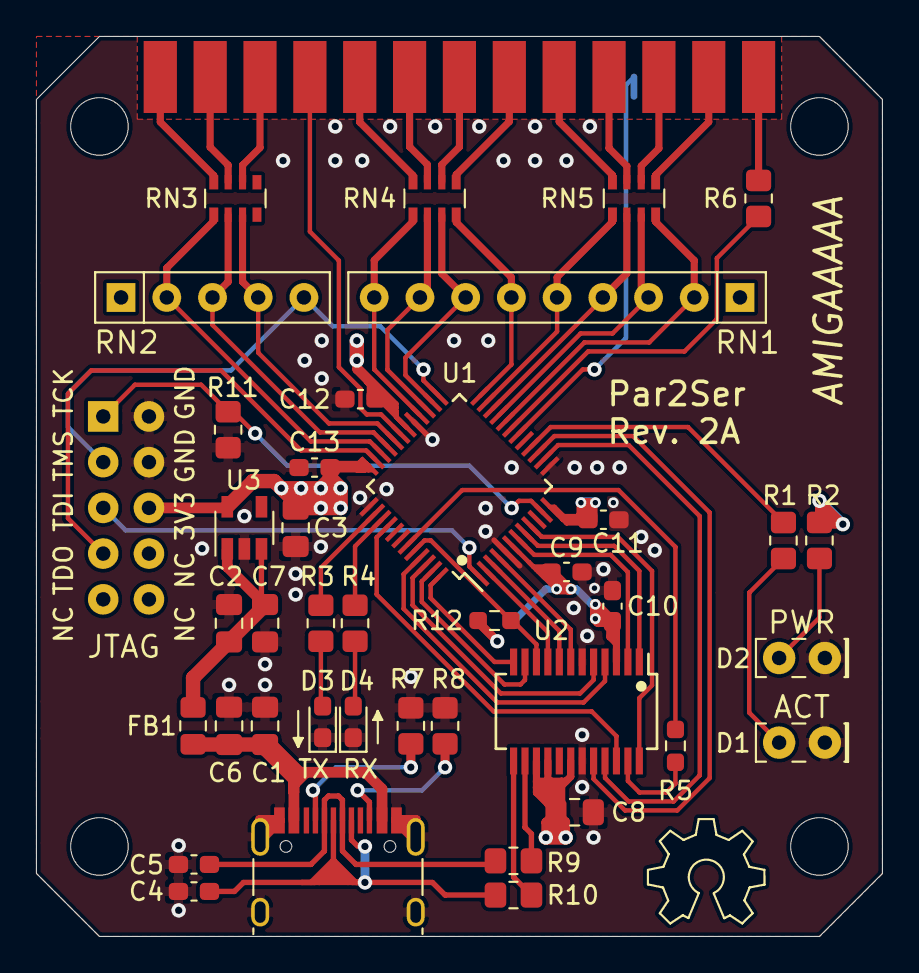
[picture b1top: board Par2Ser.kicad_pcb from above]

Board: 4 copper layers, 47.0 x 50.0 mm, 41 parts (0 on the bottom side), 63 nets.

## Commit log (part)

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2026-05-22 Add kicad files from old design
2026-05-22 Add par2ser.device serial driver (Amiga side, milestone 1)
    serial.device-compatible bridge over the parallel port using Niklas
    Ekström's 2E par-to-spi protocol toward an FT240X USB FIFO, so
    unmodified comms programs can `set line par2ser.device`.
    Built for the Bartman m68k-amiga-elf (gcc 15.1) toolchain in the style
    of jbilander/SimpleDevice: _start/romtag/RTF_AUTOINIT, register-pinned
    asm entry points over plain-C do_* workers, KPrintF tracing via debug.c.
2026-05-22 Add 3D model of USB-C connector
2026-05-22 Add LC4032V-5TN48C CPLD and remove Arduino Nano
2026-05-23 Add FT240XS-R symbol
2026-05-23 Remove unused components and begin pin assigment on CPLD, place and route pull-up resistor networks and series resistor networks for parallel port signals
2026-05-25 Replace FT232RNL with FT240X and do some routing
2026-05-26 Fix placement and routing of caps and resistors
2026-05-26 Add resistors on the two USB data lines
2026-05-26 Add 0.6/0.3 mm via
2026-05-26 Move to four layers
2026-05-27 Add remaining caps on 3V3 pins for CPLD and route power traces
2026-05-27 Add JTAG header
2026-05-27 Add 4.7k pull-down resistor on TCK and route all JTAG traces
2026-05-27 Add 3.3V regulator (TLV75533PDBVR) in SOT-23-5 package and add a 1 uF 0805 decoupling near VOUT pin and complete 3V3 routing and stitching
2026-05-27 Silkscreen fixes and add more via stitching
2026-05-28 Add .gitignore file
2026-05-28 Add README file
2026-05-28 Update .gitignore to track *.lci files
2026-05-28 feat(cpld): add Verilog implementation of Par2Ser bridge for LC4064V
    Port Niklas Ekstrom's 2E parallel protocol to the ispMACH 4000 CPLD,
    bridging the Amiga parallel port to the FT240X USB FIFO. Milestone-1
    scope: READ1/WRITE1 commands, RX-ready interrupt to CIA-A /FLAG,
    reset-aware bus tristate, and TX/RX/ACT activity LEDs.
    Fits the LC4064V-5TN48C: 59 of 64 macrocells, 50 registers, 195 pterms.
    Timing closes with large margin (worst path 5.40ns vs 83.33ns budget at
2026-05-28 Add footprint
2026-05-28 Add SIT1534AI-H4-DCC-00.032 symbol
2026-05-28 Add 32 Hz MEMS oscillator (SIT1534AI-H4-DCC-00.032) on clk3 input (pin 42)
2026-05-28 Add 3D Model of SIT1534AI-H4-DCC-00.032 MEMS Oscillator
2026-05-28 Add decoupling cap and 3.3v supply to MEMS Oscillator
2026-05-28 Add symbol for LC4064V-75TN48C CPLD
2026-05-28 chore(cpld): switch to LC4064V-75TN48C, add SiT1534 clk_slow input pin
    Switch device from the -5 speed grade to -75 in the ispLEVER project.
    Timing easily met at -75: the design's worst path at -5 was 5.40 ns
    against an 83.33 ns budget, so the ~1.5x slower -75 still has ~77 ns
    of slack. The -75 part is ~7 EUR and more widely stocked.
    Also accommodates the upcoming SiT1534 32 Hz MEMS oscillator added to
    the schematic for the LED stretcher: CBUS6 relocated to CPLD pin 40
2026-05-29 feat(cpld): one-hot FSM encoding, all three LEDs working
    Re-encode the transaction FSM from 4-bit binary to 9-bit one-hot.
    Every state == N test becomes a single wire instead of a 4-bit AND
    tree, which reduces product terms from 195 to 108 (-45%) and frees
    enough macrocells to fit all three LEDs while staying within the
    LC4064V's 64-macrocell budget.
    Behavior is preserved bit-for-bit from the previous binary FSM
2026-05-29 Remove SIT1534 (Y1) slow clock not needed
2026-05-30 Change Ohm values on R1 (1k for Yellow ACT LED) and R2 (10k for Power indicator LED) tested and verified suitable levels of glow
2026-05-30 Cosmetic fix remove OSHW copper symbol leaving cog wheel area unfilled
2026-05-30 Create LICENSE
2026-05-30 Add screenshot of device
2026-06-01 Update README.md
    Update readme with BOM for Rev. 2A
2026-06-15 feat(cpld): add SIWU# Send Immediate control on pin 44
    Add ft_siwu_n output driven by the FSM. SIWU# goes low whenever the
    FSM is in the S_CTRL state, which is entered when the Amiga issues a
    control command (D7=1, D6=1 in the command byte). This causes the
    FT240X to flush its TX buffer to USB immediately rather than waiting
    for the 16 ms latency timer.
    The S_CTRL state persists from when the command is recognized until
2026-06-15 Add screenshot images
2026-06-15 Update .gitignore to track xml files
2026-06-15 Add FT_Prog Par2Ser xml template config file
2026-06-15 docs: document FT240X validation across hosts and OSes
    Rewrite the "Programming the FT240X" section to reflect actual bring-up
    testing of the Rev 2A hardware. Adds a fast path using a supplied
    FT_PROG/Par2Ser.xml template, a manual walkthrough with screenshots,
    and a cross-OS driver-behavior table (macOS, Linux, Windows 10/11,
    Windows 8.1). Documents the Windows 8.1 quirk where a fresh host may
    bind only the bus-level driver on first plug-in, and the minimal
2026-06-17 Add images
2026-06-17 docs: add JTAG programming procedure with TCK delay fix
    Document the full JTAG bring-up procedure now that programming has been
    validated end-to-end with the FT4232H Mini Module as a generic FTDI cable.
    * Wiring table (AD0/AD1/AD2/AD3/GND → J3 pins 1/5/7/3/2|4) with
    photo of the actual hookup.
    * Note that RN2 (TMS pull-up) can be left unpopulated for initial
    bring-up since the FT4232H actively drives TMS and the LC4064V
2026-06-17 docs: clarify only Interface 0 needs the D2XX driver rebind
    ispVM only uses channel A (Interface 0) of the FT4232H Mini Module
    for JTAG. Interfaces 1/2/3 can stay bound to whatever driver they
    had previously (typically Quad RS232-HS / libusb-win32) without
    affecting programming. Also document the required restart of
    ispLEVER/ispVM after the rebind for the new driver state to take
    effect.
2026-06-20 Add schematic pdf for rev2a
2026-06-20 Add spaceclaim source file for 3D printable case
2026-06-20 Git add STEP file top and bottom of case
2026-06-20 Add Par2Ser 3D text sketchup file
2026-06-20 Add 3D printable stl files
2026-06-20 Add 3D-printable case section with CAD renders to README
2026-06-20 Fix shuffled image captions in 3D case section
2026-06-21 Add photos
2026-06-21 Document case assembly: LED fitting, finished unit, USB-C hole note
2026-06-24 Narrow USB-C cut-out for symmetric fit

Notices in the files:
KiCad/Par2Ser.kicad_pcb:
(C) 2024,2026
